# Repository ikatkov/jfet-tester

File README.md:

# JFET tester

See https://sound-au.com/articles/jfet-design.htm

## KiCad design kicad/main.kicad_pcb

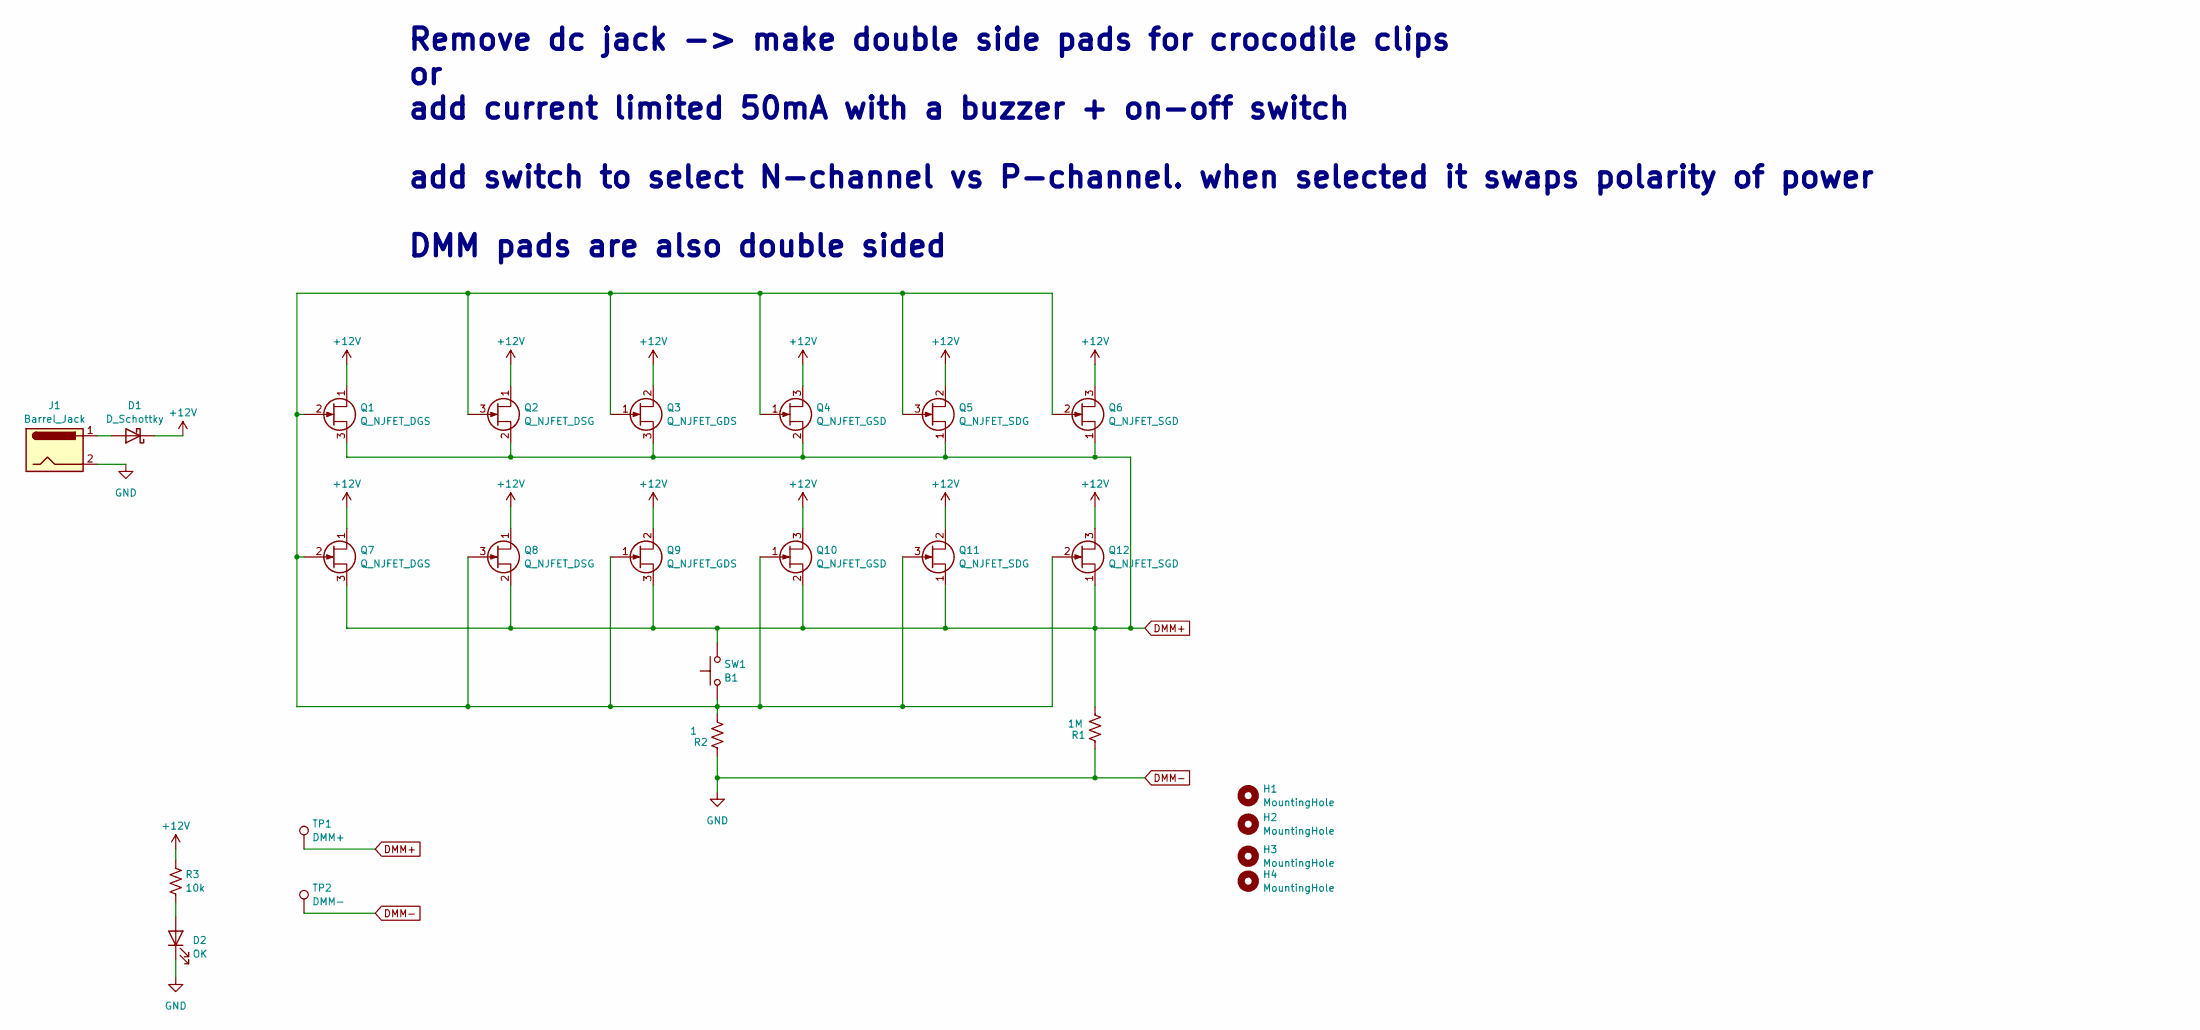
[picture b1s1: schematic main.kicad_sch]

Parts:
D1: D_Schottky; D_MiniMELF
D2: OK; LED_D5.0mm
H1, H2, H3, H4: MountingHole; MountingHole_3.2mm_M3
J1: Barrel_Jack; BarrelJack_Horizontal
Q1: Q_NJFET_DGS; TO-92_Inline_Wide
Q2: Q_NJFET_DSG; TO-92_Inline_Wide
Q3: Q_NJFET_GDS; TO-92_Inline_Wide
Q4: Q_NJFET_GSD; TO-92_Inline_Wide
Q5: Q_NJFET_SDG; TO-92_Inline_Wide
Q6: Q_NJFET_SGD; TO-92_Inline_Wide
Q7: Q_NJFET_DGS; SOT-23_Handsoldering
Q8: Q_NJFET_DSG; SOT-23_Handsoldering
Q9: Q_NJFET_GDS; SOT-23_Handsoldering
Q10: Q_NJFET_GSD; SOT-23_Handsoldering
Q11: Q_NJFET_SDG; SOT-23_Handsoldering
Q12: Q_NJFET_SGD; SOT-23_Handsoldering
R1: 1M; R_0805_2012Metric
R2: 1; R_0805_2012Metric
R3: 10k; R_0805_2012Metric
SW1: B1; SW_PUSH_6mm
TP1: DMM+; PinSocket_1x02_P2.54mm_Vertical
TP2: DMM-; PinSocket_1x02_P2.54mm_Vertical

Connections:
+12V: D1.1 (K), Q1.1 (D), Q2.1 (D), Q3.2 (D), Q4.3 (D), Q5.2 (D), Q6.3 (D), Q7.1 (D), Q8.1 (D), Q9.2 (D), Q10.3 (D), Q11.2 (D), Q12.3 (D), R3.1
DMM+: Q1.3 (S), Q2.2 (S), Q3.3 (S), Q4.2 (S), Q5.1 (S), Q6.1 (S), Q7.3 (S), Q8.2 (S), Q9.3 (S), Q10.2 (S), Q11.1 (S), Q12.1 (S), R1.1, SW1.2, TP1.1
DMM-: D2.1 (K), J1.2, R1.2, R2.2, TP2.1
unnamed: D1.2 (A), J1.1
unnamed: D2.2 (A), R3.2
unnamed: Q1.2 (G), Q2.3 (G), Q3.1 (G), Q4.1 (G), Q5.3 (G), Q6.2 (G), Q7.2 (G), Q8.3 (G), Q9.1 (G), Q10.1 (G), Q11.3 (G), Q12.2 (G), R2.1, SW1.1

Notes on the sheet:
Remove dc jack -> make double side pads for crocodile clips or add current limited 50mA with a buzzer + on-off switch add switch to select N-channel vs P-channel. when selected it swaps polarity of power DMM pads are also double sided

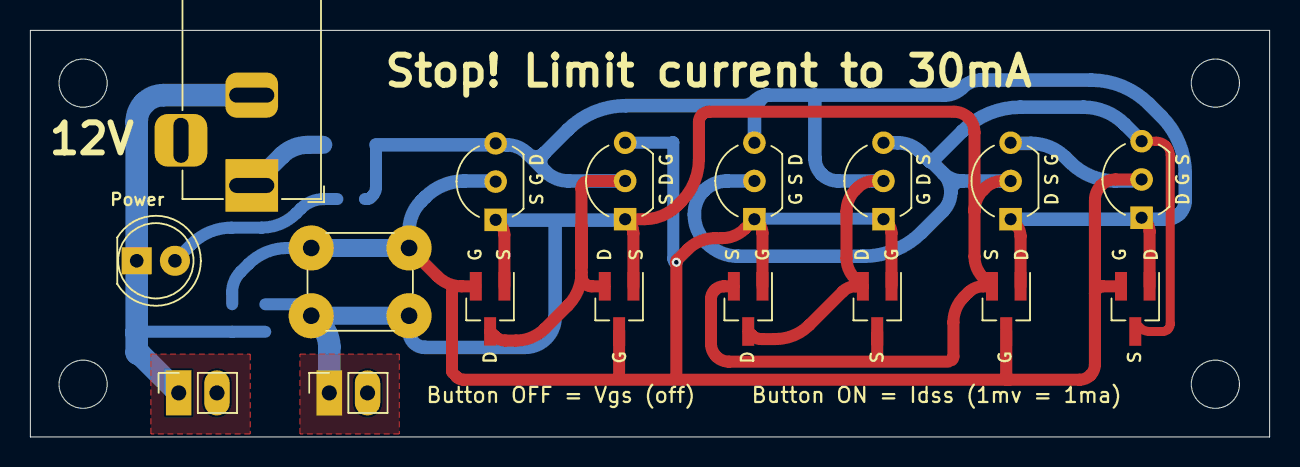
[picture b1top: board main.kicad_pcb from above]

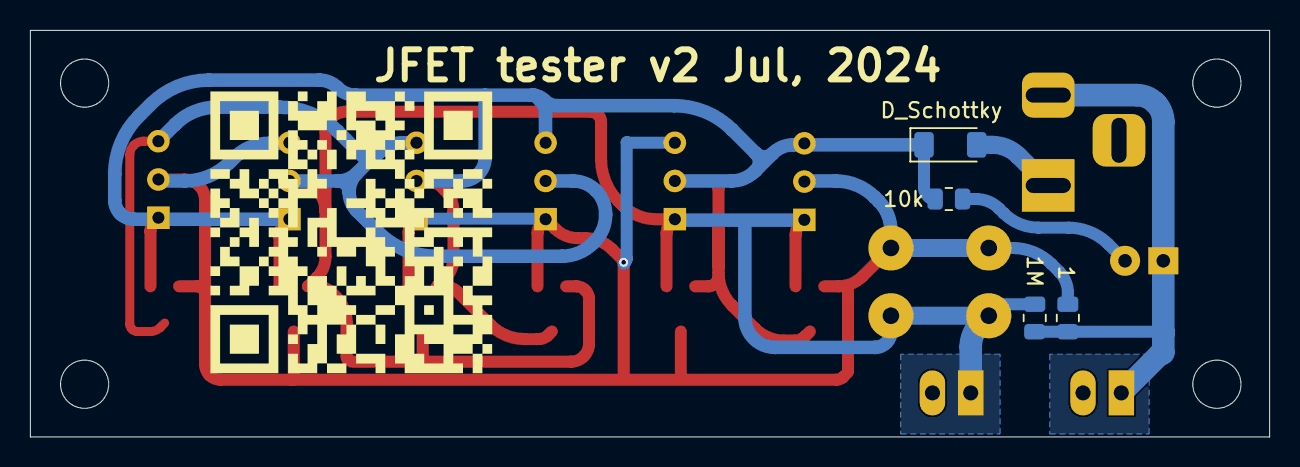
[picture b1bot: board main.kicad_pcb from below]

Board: 4 copper layers, 82.3 x 27.0 mm, 25 parts (4 on the bottom side), 6 nets.

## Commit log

2024-07-27 added qrcode
2024-09-07 wider pinout
